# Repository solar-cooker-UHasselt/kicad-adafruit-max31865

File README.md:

# kicad-adafruit-max31865

A breakout board for the MAX31865, an amplifier and converter for PT100 platinum RTD
temperature probes. It has a 430 Ω reference resistor, solder jumpers for 2, 3 or 4 wire
probes, a screw terminal for the probe, and a 3.3 V regulator and level shifting so it
works with 3.3 V and 5 V boards. It is a KiCad 10 port of
[Adafruit's MAX31865 breakout](https://github.com/adafruit/Adafruit-MAX31865-PCB),
originally drawn in Eagle.

In the [solar cooker](https://github.com/solar-cooker-UHasselt) testing station, the
firmware ([arduino-code](https://github.com/solar-cooker-UHasselt/arduino-code)) reads
the temperature of three 4-wire PT100 probes over SPI, one board per probe.

- [Board page](https://solar-cooker-uhasselt.github.io/kicad-adafruit-max31865/): 3D
  renders, drawings, schematic and board PDF, interactive BOM and the BOM CSV for
  Eurocircuits, rebuilt by CI on every push to `main`
- [PCB source](https://github.com/adafruit/Adafruit-MAX31865-PCB): Adafruit's Eagle
  files
- [Adafruit guide](https://learn.adafruit.com/adafruit-max31865-rtd-pt100-amplifier):
  pinout, wiring, the jumpers for 2, 3 or 4 wires and Arduino examples

## Installation

### Requirements

- [KiCad 10](https://www.kicad.org/download/), to open and edit the board
- [git](https://git-scm.com), to clone the repo
- Optional, for the checks: [just](https://just.systems)

### Clone

```bash
git clone https://github.com/solar-cooker-UHasselt/kicad-adafruit-max31865.git
```

Own symbols, footprints and 3D models are in `external/`, in the repo itself.

## Usage

Open `MAX31865.kicad_pro` in KiCad 10. The schematic and board open from there.

Before committing, run ERC and DRC, reports in `tmp/`:

```bash
just check
```

`just --list` shows the other recipes: PDFs, and the CI workflow run locally.

## Contributing

Branches, pull requests, approval and commits work as in every repo of the org, see
[CONTRIBUTING.md](https://github.com/solar-cooker-UHasselt/.github/blob/main/.github/CONTRIBUTING.md).
Specific to this repo:

- CI runs ERC and DRC on every pull request, through the shared workflows in
  [kicad-ci](https://github.com/solar-cooker-UHasselt/kicad-ci). A push to `main` that
  changes more than Markdown also rebuilds the board page.
- Types, scopes and the ERC/DRC check for commits are in
  [.agents/commit_conventions.md](.agents/commit_conventions.md).
- Changes to the board setup, CI or docs are made and tested in
  [kicad-adafruit-ds3231](https://github.com/solar-cooker-UHasselt/kicad-adafruit-ds3231)
  first, then copied here.

## Authors and acknowledgment

The board is Adafruit's design, by Limor Fried/Ladyada for Adafruit Industries
([PCB source](https://github.com/adafruit/Adafruit-MAX31865-PCB)). The KiCad 10 port is
by Lowie Van Vyve for the UHasselt solar cooker project.

Adafruit invests time and resources providing this open source design. Please support
Adafruit and open-source hardware by purchasing products from
[Adafruit](https://www.adafruit.com).

<details>
<summary>Adafruit's original README, included as its license asks</summary>

> **Adafruit MAX31865 PCB**
>
> [Click here to purchase one from the Adafruit shop](http://www.adafruit.com/products/3328)
>
> PCB files for the Adafruit MAX31865 RTD Sensor Breakout. Format is EagleCAD schematic
> and board layout
>
> - https://www.adafruit.com/product/3328
>
> **Description**
>
> For precision temperature sensing, nothing beats a Platinum RTD. Resistance
> temperature detectors (RTDs) are temperature sensors that contain a resistor that
> changes resistance value as its temperature changes, basically a kind of thermistor.
> In this sensor, the resistor is actually a small strip of Platinum with a resistance
> of 100 ohms at 0°C, thus the name PT100. Compared to most NTC/PTC thermistors, the PT
> type of RTD is much most stable and precise (but also more expensive) PT100's have
> been used for many years to measure temperature in laboratory and industrial
> processes, and have developed a reputation for accuracy (better than thermocouples),
> repeatability, and stability.
>
> However, to get that precision and accuracy out of your PT100 RTD you must use an
> amplifier that is designed to read the low resistance. Better yet, have an amplifier
> that can automatically adjust and compensate for the resistance of the connecting
> wires. If you're looking for a great RTD sensor, today is your lucky day because we
> have a lovely Adafruit RTD Sensor Amplifier with the MAX31865 breakout for use with
> any 2, 3 or 4 wire PT100 RTD!
>
> **License**
>
> Adafruit invests time and resources providing this open source design, please support
> Adafruit and open-source hardware by purchasing products from
> [Adafruit](https://www.adafruit.com)!
>
> Designed by Limor Fried/Ladyada for Adafruit Industries.
>
> Creative Commons Attribution/Share-Alike, all text above must be included in any
> redistribution. See license.txt for additional details.

</details>

## License

[CC BY-SA 4.0](LICENSE). Adafruit's original design is licensed CC BY-SA 3.0, which
allows adaptations like this port under a later version with the same terms.

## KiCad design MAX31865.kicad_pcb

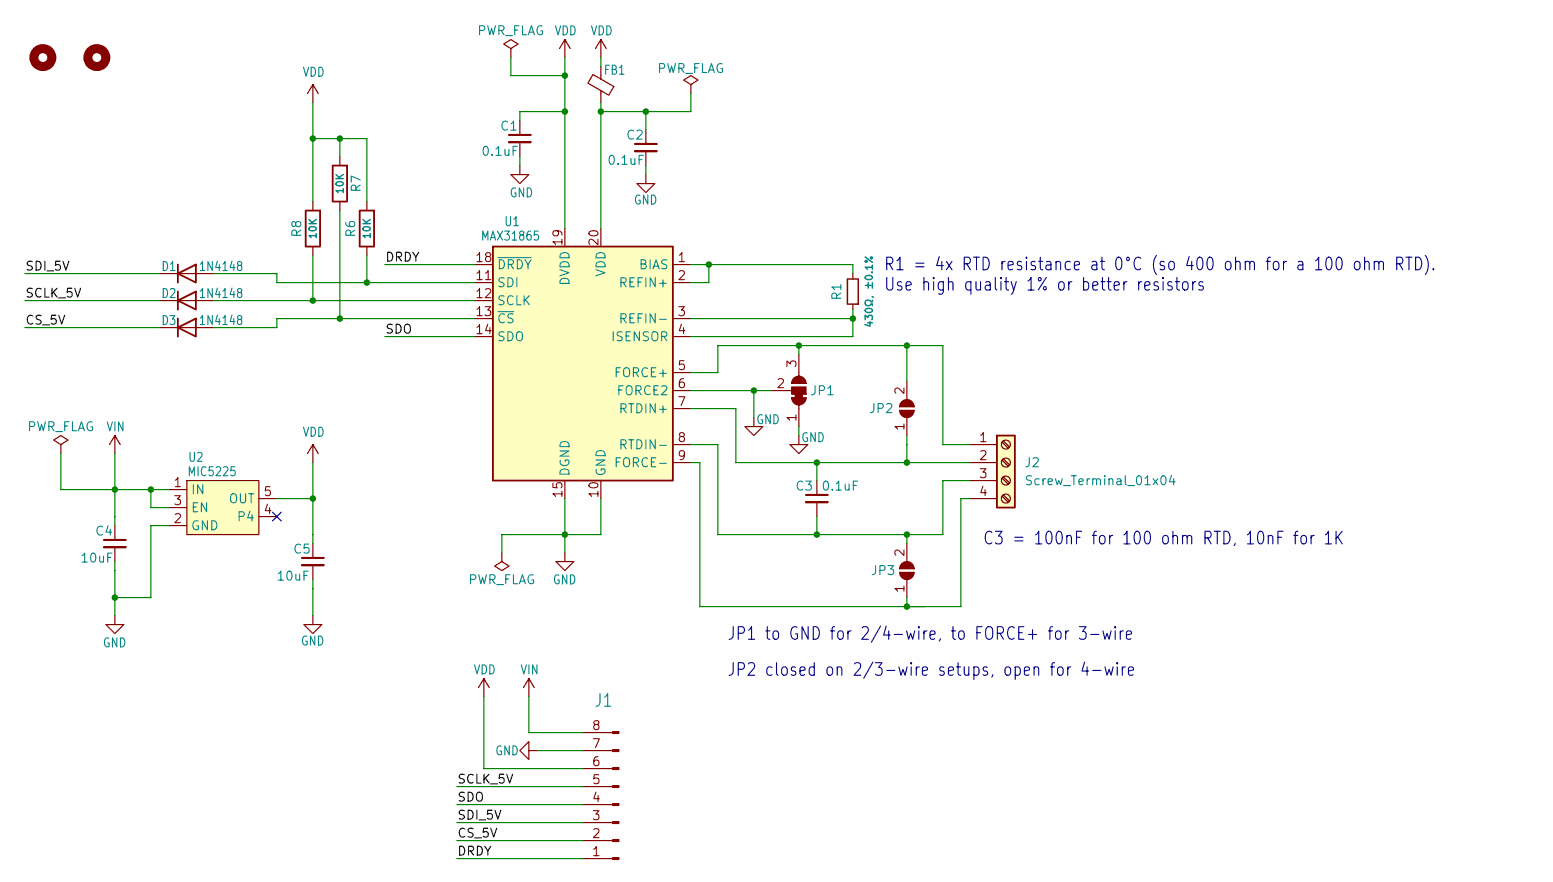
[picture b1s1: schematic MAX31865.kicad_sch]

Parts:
C1, C2, C3: 0.1uF; C_0805_2012Metric; MPN /
C4, C5: 10uF; C_0805_2012Metric; MPN /
D1, D2, D3: 1N4148; D_SOD-323; MPN 1N4148WX-TP
FB1: FERRITE-0805NO; LI0805G201R-10; MPN LI0805G201R-10
J1: connector; PinHeader_1x08_P2.54mm_Vertical; MPN TSW-108-09-G-S
J2: Screw_Terminal_01x04; TerminalBlock_4Ucon_1x04_P3.50mm_Horizontal; MPN 039357-0004
JP1: SolderJumper_3_Bridged12; SolderJumper-3_P1.3mm_Bridged12_Pad1.0x1.5mm
JP2, JP3: SOLDERJUMPER; SolderJumper-2_P1.3mm_Open_RoundedPad1.0x1.5mm
R1: 430Ω, ±0.1%; R_0805_2012Metric; MPN /
R6, R7, R8: 10K; R_0805_2012Metric; MPN /
U1: MAX31865; MAX31865ATP+; MPN MAX31865ATP+
U2: MIC5225; SOT-23-5; MPN MIC5225-3.3YM5-TR
U$18, U$19: MOUNTINGHOLE2.5; MountingHole_2.2mm_M2_ISO7380

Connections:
/CS_5V: D3.1 (K), J1.2
/DRDY: J1.1, U1.18 (~DRDY)
/SCLK_5V: D2.1 (K), J1.5
/SDI_5V: D1.1 (K), J1.3
/SDO: J1.4, U1.14 (SDO)
GND: C1.2, C2.2, C4.2, C5.2, J1.7, JP1.1 (A), JP1.2 (C), U1.6 (FORCE2), U1.10 (GND), U1.15 (DGND), U1.16 (GND), U1.21 (GND), U2.2 (GND)
unnamed: D1.2 (A), R6.1, U1.11 (SDI)
unnamed: D2.2 (A), R8.1, U1.12 (SCLK)
unnamed: D3.2 (A), R7.1, U1.13 (~CS)
unnamed: J2.1, JP1.3 (B), JP2.2 (B), U1.5 (FORCE+)
unnamed: C3.1, J2.2, JP2.1 (A), U1.7 (RTDIN+)
unnamed: C3.2, J2.3, JP3.2 (B), U1.8 (RTDIN-)
unnamed: J2.4, JP3.1 (A), U1.9 (FORCE-)
unnamed: R1.2, U1.1 (BIAS), U1.2 (REFIN+)
unnamed: R1.1, U1.3 (REFIN-), U1.4 (ISENSOR)
unnamed: C2.1, FB1.1, U1.20 (VDD)
VDD: C1.1, C5.1, FB1.2, J1.6, R6.2, R7.2, R8.2, U1.19 (DVDD), U2.5 (OUT)
VIN: C4.1, J1.8, U2.1 (IN), U2.3 (EN)

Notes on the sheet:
JP1 to GND for 2/4-wire, to FORCE+ for 3-wire
R1 = 4x RTD resistance at 0°C (so 400 ohm for a 100 ohm RTD). Use high quality 1% or better resistors
C3 = 100nF for 100 ohm RTD, 10nF for 1K
JP2 closed on 2/3-wire setups, open for 4-wire

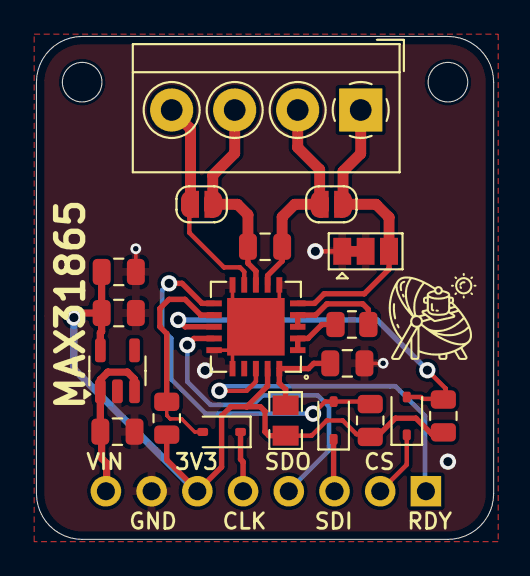
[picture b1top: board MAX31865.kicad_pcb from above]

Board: 2 copper layers, 25.4 x 27.9 mm, 22 parts (1 on the bottom side), 18 nets.

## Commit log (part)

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2024-03-28 temp
